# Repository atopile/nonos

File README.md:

# NONOS

### The Open Source Smart Speaker

<div align="center">

  **Premium Sound • Privacy First • Fully Hackable**

</div>

---

## 🎵 Experience Audio Freedom

NONOS is a premium smart speaker that puts you in control. It delivers exceptional sound quality while respecting your privacy, and its hardware is described declaratively in lightweight `.ato` files.

### ✨ Key Features

<table>
<tr>
<td width="50%">

**🔊 Audiophile-Grade Sound**

- Dual-driver system with dedicated tweeter and full-range speaker
- Texas Instruments TAS5825M Class-D amplifier
- Analog Devices ADAU145x DSP for pristine audio processing
- I2S digital audio interface for lossless playback

</td>
<td width="50%">

**🧠 Powerful Computing**

- Raspberry Pi CM5 module at its heart
- Gigabit Ethernet connectivity
- USB-C with Power Delivery support
- Multiple I2C, UART, and GPIO interfaces

</td>
</tr>
<tr>
<td width="50%">

**🎨 Interactive Design**

- 23 SK6805 addressable RGB LEDs
- Capacitive touch controls with volume slider
- NFC tap-to-pair functionality
- Minimalist cylindrical form factor

</td>
<td width="50%">

**⚡ Smart Power Management**

- USB-C Power Delivery (20V input)
- Efficient buck converters (5V & 3.3V rails)
- STUSB4500 PD controller
- Low standby power consumption

</td>
</tr>
</table>

---

## 🎶 Software Features

### Streaming Services

Connect and play from all your favorite sources:

- **Spotify Connect** - Stream directly from the Spotify app
- **AirPlay** - Native support for Apple devices
- **Bluetooth Audio** - Auto-pairing A2DP streaming
- **Local Playback** - Play your music library via network shares

### Smart Controls

Intuitive touch interface with gesture support:

- **Play/Pause** - Center button for media control
- **Track Navigation** - Skip tracks or seek within songs
- **Volume Slider** - 5-position touch slider with double-tap gestures
  - Double-tap position 0 for mute
  - Double-tap position 4 for +6dB boost
- **Configurable EQ** - 15-band parametric equalizer

### Audio Excellence

Professional-grade DSP processing:

- **Crossover Networks** - Optimized for dual-driver configuration
- **Dynamic Range Control** - Independent limiting for highs and lows
- **Mid-Side Processing** - Adjustable stereo width
- **PipeWire Integration** - Low-latency audio with automatic resampling

---

## 🎛️ Hardware Highlights

### Audio Processing Pipeline

```
CM5 (Digital Audio) → I2S → ADAU145x DSP → I2S → TAS5825M Amplifier → Speakers
```

### Interactive Hat Module

- **NFC**: PN5321 for instant device pairing
- **Touch**: CAP1188 capacitive sensor (3 buttons + 5-position slider)
- **LEDs**: 23x SK6805 RGB LEDs in a circular array
- **Level Shifting**: Ensures reliable 3.3V/5V communication

### Debug Headers

Three Saleae-compatible headers for easy development:

- UART console access
- I2C bus monitoring
- I2S audio stream analysis

### Printed Circuit Boards

#### Mainboard

- **atopile module:** `NONOS` (`elec/src/nonos.ato`)
- USB-C Power Delivery input via **STUSB4500** (up to 20 V)
- Power tree: **TPS54560x** 5 V buck ➜ **TLV75901** 3 .3 V LDO
- **Raspberry Pi CM5** compute module
- **ADAU145x** audio DSP ➜ **TAS5825M** 2-channel Class-D amplifier
- 10-pin mezzanine connector to the Hat
- Connectors for full-range & tweeter speakers
- Three Saleae-compatible debug headers (UART, I2C, I2S)

#### Control Hat

- **atopile module:** `Hat` (`elec/src/hat.ato`)
- **PN5321** NFC transceiver with custom button-antenna
- **CAP1188** capacitive touch sensor (3 buttons + 5-point slider)
- 23× **SK6805** side-emitting RGB LEDs arranged in a ring
- **74LVC1T45** level-shifter for reliable 5 V LED data
- Powered from 3 .3 V (logic) & 5 V (LEDs) supplied by the mainboard
- 10-pin mezzanine connector mates directly with the mainboard

---

## 🛠️ Hardware Design

The hardware is captured in concise `.ato` design files (powered by [atopile](https://atopile.io)).

```ato
module NONOS:
    """
    An opensource sonos era 100 clone
    """

    # Core Components
    cm5 = new CM5
    amplifier = new Texas_Instruments_TAS5825MRHBR_driver
    dsp = new Analog_Devices_ADAU145x_driver
    pd_controller = new STUSB4500

    # Smart Power Distribution
    pd_controller.power_out ~ power_20v
    power_20v ~> regulator_5v ~> power_5v
    power_5v ~> regulator_3v3 ~> power_3v3
```

### 📁 Project Structure

```
nonos/
├── elec/
│   └── src/
│       ├── nonos.ato      # Main speaker module
│       ├── hat.ato        # Touch/LED/NFC interface
│       └── parts/         # Component library
├── firmware/              # CM5 software stack
├── mechanical/            # Enclosure designs
└── docs/                  # Build instructions
```

---

## 🎚️ Audio Tuning

<table>
<tr>
<td width="33%"></td>
<td width="33%"></td>
<td width="33%"></td>
</tr>
</table>

Using a calibrated reference microphone we swept each driver, loaded the recordings into **Audacity** to eyeball the bumps and dips, then built FIR/biquad filters in SigmaStudio and dialed-in a 2-way crossover with gentle EQ to flatten the combined response. The whole process took about **20 heroic minutes**—roughly _twice_ the time it looks like Sonos spends on some of their launch-day tunings 😉.

---

## 🚀 Getting Started

### Prerequisites

- **[atopile](https://docs.atopile.io/atopile/quickstart)** compiler installed
- KiCad 8.0 or later (for PCB viewing/editing)
- Basic SMD soldering equipment

### Building NONOS

1. **Clone the repository**

   ```bash
   git clone https://github.com/atopile/nonos
   cd nonos
   ```

2. **Compile the hardware design**

   ```bash
   ato build
   ```

3. **Generate manufacturing files**

   ```bash
   ato build -t all
   ```

4. **Order PCBs and components**
   - Upload gerbers from `/build` to your preferred PCB manufacturer
   - Use the generated BOM for component ordering

---

## 🤝 Contributing

We love contributions! Whether it's:

- 🐛 Bug fixes
- ✨ New features
- 📚 Documentation improvements
- 🎨 Design enhancements

---

## 📄 License

NONOS is open source hardware, released under the MIT License. See [LICENSE](LICENSE) for details.

---

## 🌟 Acknowledgments

Built with ❤️ using **[atopile](https://atopile.io)** - the language that's revolutionizing hardware design.

Special thanks to the atopile community for making hardware development accessible to everyone.

---

<div align="center">
  
**Ready to build your own NONOS?**

[📖 Read the Docs](https://github.com/atopile/nonos) • [💬 Join Discord](https://discord.gg/7XSb5zTyfr) • [⭐ Star on GitHub](https://github.com/atopile/nonos)

</div>

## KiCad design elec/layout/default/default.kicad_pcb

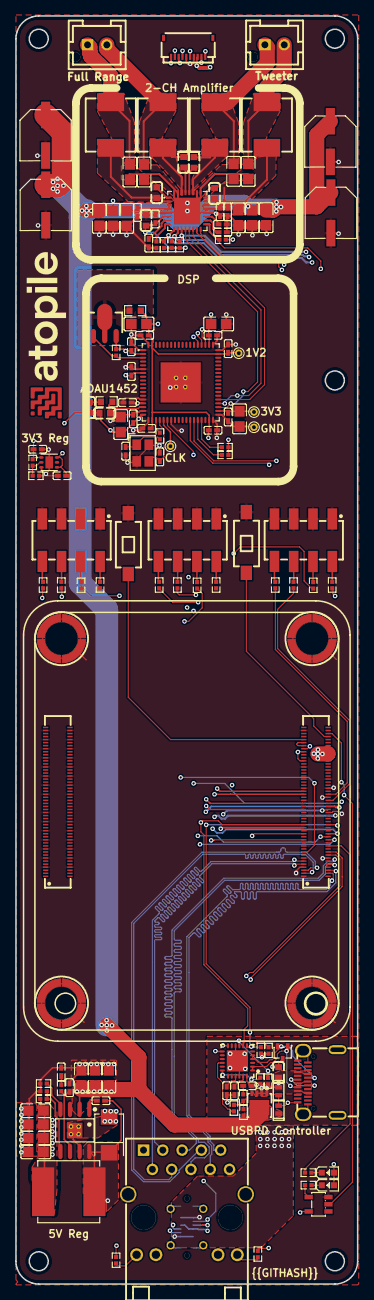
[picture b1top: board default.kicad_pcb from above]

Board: 4 copper layers, 45.0 x 167.0 mm, 141 parts (1 on the bottom side), 106 nets.

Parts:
C1, C4, C19, C21, C22, C31, C32: 1µF ±10% 25V X5R; C0402
C2: 4.7µF ±10% 16V X5R; C0603
C3, C33, C38, C39, C40, C41, C42, C43, C44, C45, C46, C47, C53, C54, C55: 100nF ±10% 16V X7R; C0402
C5, C6, C9, C10: 470nF ±10% 50V X7R; C0603
C7, C8, C11, C12: 680nF ±10% 50V X7R; C0805
C13, C14, C15, C16, C17, C18, C34, C35, C36, C37: 10µF ±10% 25V X5R; C0805
C20: 100nF ±10% 50V X7R; C0402
C23: 4.7nF ±5% 50V X7R; C0402
C24: 20pF ±5% 50V C0G; C0402
C25, C26, C27: 10µF ±10% 50V X5R; C0805
C28, C29, C52, C60: 22µF ±20% 25V X5R; C0805
C30: 4.7µF ±10% 35V X5R; C0603
C48, C49: 15pF ±5% 50V C0G; C0402
C50: 5.6nF ±10% 50V X7R; C0603
C51: 150pF ±5% 50V C0G; C0603
C56, C57, C58, C59: CAP-SMD_BD6.3-L6.6-W6.6-FD
CN1, CN2: CONN-SMD_DF40C-100DS-0.4V-51
D1: LED0603-RD-YELLOW
D2: LED0603-RD
D3: SMB_L4.6-W3.6-LS5.3-RD
D4: SOT-323-3_L2.1-W1.3-P1.32-LS2.1-BR
D5, D6: DFN1610-2_L1.6-W1.0-P1.05-RD
FPC1: FPC-SMD_10P-P0.50_HDGC_0.5K-HX-10PWB
HDR1, HDR2, HDR3: HDR-SMD_8P-P2.54-V-M-R2-C4-LS7.4
L1, L2, L3, L4: 10µH ±20% 4.5A 68mΩ; IND-SMD_L7.3-W6.8
L5: IND-SMD_L8.0-W8.0_SWPA8040S
Q1: PDFN3333-8_L3.1-W3.2-P0.65-LS3.4-BL
Q2: SOT-89-3_L4.5-W2.5-P1.50-LS4.1-TR
R1, R15, R16: 4.7kΩ ±1% 62.5mW; R0402
R2, R3, R4, R5, R35, R37, R40, R41: 10kΩ ±1% 62.5mW; R0402
R6, R7: 2kΩ ±1% 62.5mW; R0402
R8, R9: 470Ω ±1% 62.5mW; R0402
R10: 23.7kΩ ±1% 62.5mW; R0402
R11, R12, R14, R17, R24, R25, R26, R27, R28, R29, R30, R31, R32, R33, R34: 1kΩ ±1% 62.5mW; R0402
R13: 162kΩ ±1% 62.5mW; R0402
R18: 100kΩ ±1% 62.5mW; R0402
R19: 22kΩ ±1% 62.5mW; R0402
R20, R21: 100Ω ±1% 62.5mW; R0402
R22: 0Ω 100mW; R0603
R23: 4.3kΩ ±1% 100mW; R0603
R36: 47kΩ ±1% 62.5mW; R0402
R38: 54.9kΩ ±1% 62.5mW; R0402
RJ1: RJ45-TH_HR911130A
SW1, SW2: SW-SMD_L6.0-W3.3-LS8.0
TP1, TP2, TP3, TP4: TestPoint_THTPad_D1.0mm_Drill0.5mm
U1: VQFN-32_L5.0-W5.0-P0.50-TL-EP
U2: SOT-23-5_L3.0-W1.7-P0.95-LS2.8-BR
U3, U4, U5, U6: SMD_BD5.6-D4.1
U7: SOIC-8_L5.0-W4.0-P1.27-LS6.0-BL-EP2.0
U20: QFN-24_L4.0-W4.0-P0.50-BL-EP2.8
U21, U22: CONN-TH_B02B-XASK-1-A-LF-SN
U23: USB-C-SMD_HC-TYPE-C-24P-VS9.3-5A-F1.1-04
U24: LFCSP-72_L10.0-W10.0-P0.50-LS10.2-BL-EP5.3
U25: WSON-6_L2.0-W2.0-P0.65-TL-EP
USB1: USB-C-SMD_TYC-324G
X1: CRYSTAL-SMD_4P-L3.2-W2.5-BL-2

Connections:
3v3_vcc: C2.1, C3.1, C22.1, C34.1, C35.1, C37.1, C38.1, C43.1, C44.1, C45.1, C46.1, C47.1, C50.2, C51.2, CN1.39, CN1.42, CN1.43, D1.2, D2.2, FPC1.6, Q2.1, R2.2, R3.2, R4.2, R5.2, R8.1, R9.1, R11.1, R15.2, R16.2, R24.1, R36.1, R40.2, R41.2, TP3.1, U1.6, U2.5, U24.2, U24.7, U24.15, U24.18, U24.38, U24.56, U25.1
5v_vcc: C21.1, C28.1, C29.1, C52.1, C60.1, CN1.57, CN1.58, CN1.59, CN1.60, CN1.61, CN1.62, FPC1.8, L5.2, R12.1, R38.1, U25.4, U25.6
20v_vcc: C13.1, C14.1, C15.1, C16.1, C17.1, C18.1, C25.1, C26.1, C27.1, C53.1, C54.1, C55.1, C56.1, C57.1, C58.1, C59.1, D6.1, Q1.5, Q1.6, Q1.7, Q1.8, Q1.9, R18.2, U1.3, U1.4, U1.21, U1.22, U7.2
A5: D4.1, U20.1, U20.2, U23.A5, USB1.A5
ADR: R1.1, U1.8
AVDD: C1.1, U1.19
B5: D4.2, U20.4, U20.5, U23.B5, USB1.B5
BOOT: C20.1, U7.1
BST_Aneg_N: C5.1, U1.29
BST_Apos_P: C6.1, U1.1
BST_Bneg_N: C9.1, U1.28
BST_Bpos_P: C10.1, U1.24
CLKOUT: TP1.1, U24.23
COMP: C24.1, R10.1, U7.6
DISCH: R14.2, U20.9
ETH_LED_LINK: CN1.93, RJ1.12
ETH_LED_SPEED: CN1.92, RJ1.13
ETH_P0_N: CN1.5, RJ1.P3
ETH_P0_P: CN1.6, RJ1.P2
ETH_P1_N: CN1.3, RJ1.P7
ETH_P1_P: CN1.2, RJ1.P4
ETH_P2_N: CN1.96, RJ1.P6
ETH_P2_P: CN1.95, RJ1.P5
ETH_P3_N: CN1.98, RJ1.P9
ETH_P3_P: CN1.99, RJ1.P8
GVDD: C4.1, U1.18
OUT_Aneg_N: C5.2, L1.1, U1.30
OUT_Apos_P: C6.2, L2.1, U1.2
OUT_Bneg_N: C9.2, L3.1, U1.27
OUT_Bpos_P: C10.2, L4.1, U1.23
PLLFILT: C51.1, R23.1, U24.16
RT_CLK: R13.1, U7.4
RX: CN1.73, R26.1
VBUS_EN_SNK: R19.2, U20.16
VBUS_VS_DISCH: R17.2, U20.18
VDRIVE: Q2.3, R24.2, U24.3
VREG_1V2-VCC: C31.2, U20.21
VREG_2V7-VCC: C32.2, U20.23
VR_DIG: C19.1, U1.7
XTALIN_MCLK: R21.1, U24.21
XTALOUT: C49.1, U24.22, X1.3
Y: R7.2, U2.4
activity_led-cathode: D1.1, R6.1
activity_led_resistor-pins[20]: CN1.90, R6.2
address_bit_0: R40.1, U24.33
address_bit_1: R41.1, U24.32
amp_fault: CN1.17, R2.1, U1.9
amp_i2s_sck: U1.13, U24.40
amp_i2s_sd: U1.14, U24.41
amp_i2s_ws: U1.12, U24.39
amp_mute: CN1.78, R3.1, U1.10
amp_pdn: CN1.15, R4.1, U1.17
amp_warn: CN1.80, R5.1, U1.11
boot_mode: CN1.54, SW1.1
bootstrap_capacitor-cathode: C20.2, D3.1, L5.1, U7.8
c1-net: C50.1, R23.2
cm5-anode-0: R8.2, RJ1.11
cm5-anode-1: R9.2, RJ1.14
cm5-cathode: D2.1, R7.1
collector: Q2.2, R22.1
compensation_capacitors[0]-net: C23.1, R10.2
debug_headers[0]-_2: HDR1.2, R11.2
debug_headers[0]-_4: HDR1.4, R12.2
debug_headers[0]-_6: HDR1.6, R25.2
debug_headers[0]-_8: HDR1.8, R26.2
debug_headers[1]-_2: HDR2.2, R27.2
debug_headers[1]-_4: HDR2.4, R28.2
debug_headers[1]-_6: HDR2.6, R29.2
debug_headers[1]-_8: HDR2.8, R30.2
debug_headers[2]-_2: HDR3.2, R31.2
debug_headers[2]-_4: HDR3.4, R32.2
debug_headers[2]-_6: HDR3.6, R33.2
debug_headers[2]-_8: HDR3.8, R34.2
dsp_reset_disable: CN1.87, U24.24
eth_sync_out: CN1.9, R28.1
feedback_divider-output-VDIV_OUTPUT-0: R35.1, R36.2, U25.2
feedback_divider-output-VDIV_OUTPUT-1: R37.1, R38.2, U7.5
footprint-net-2: C33.1, R20.2
gate: Q1.4, R18.1, R19.1, R20.1
gnd: C1.2, C2.2, C3.2, C4.2, C7.2, C8.2, C11.2, C12.2, C13.2, C14.2, C15.2, C16.2, C17.2, C18.2, C19.2, C21.2, C22.2, C23.2, C24.2, C25.2, C26.2, C27.2, C28.2, C29.2, C30.1, C31.1, C32.1, C34.2, C35.2, C36.2, C37.2, C38.2, C39.2, C40.2, C41.2, C42.2, C43.2, C44.2, C45.2, C46.2, C47.2, C48.2, C49.2, C52.2, C53.2, C54.2, C55.2, C56.2, C57.2, C58.2, C59.2, C60.2, CN1.1, CN1.4, CN1.7, CN1.11, CN1.16, CN1.21, CN1.26, CN1.30, CN1.33, CN1.37, CN1.49, CN1.65, CN1.68, CN1.71, CN1.74, CN1.79, CN1.84, CN1.89, CN1.94, CN1.97, CN1.100, CN2.4, CN2.7, CN2.10, CN2.13, CN2.16, CN2.19, CN2.22, CN2.28, CN2.31, CN2.34, CN2.37, CN2.40, CN2.43, CN2.46, CN2.49, CN2.52, CN2.55, CN2.58, CN2.61, CN2.64, CN2.67, CN2.70, CN2.73, CN2.82, CN2.85, CN2.88, CN2.91, CN2.94, CN2.97, D3.2, D4.3, D5.2, D6.2, FPC1.5, FPC1.7, HDR1.1, HDR1.3, HDR1.5, HDR1.7, HDR2.1, HDR2.3, HDR2.5, HDR2.7, HDR3.1, HDR3.3, HDR3.5, HDR3.7, R1.2, R13.2, R35.2, R37.2, RJ1.SHIELD0, RJ1.SHIELD1, SW1.2, SW2.2, TP2.1, U1.5, U1.20, U1.25, U1.26, U1.31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
i2c-SCL: CN1.83, R15.1, R30.1, U1.16, U20.7, U24.31
i2c-SCLK: CN1.18, R16.1, R29.1, U1.15, U20.8, U24.30
i2cs[1]-SCL: CN1.28, FPC1.9
i2cs[1]-SDA: CN1.29, FPC1.10
i2s_ins[0]-SCK: CN1.76, R34.1, U24.57
i2s_ins[0]-SD: CN1.88, R32.1, U24.59
i2s_ins[0]-WS: CN1.13, R33.1, U24.58
input-pins[94]: CN1.53, U2.2
led_data: CN1.77, FPC1.1
nOE: C48.1, R21.2, X1.1
nfc_interrupt: CN1.25, FPC1.3
nfc_reset: CN1.86, FPC1.4
power_1v8-VCC: CN1.44, CN1.45
power_button: CN1.46, SW2.1
power_digital-VCC: C36.1, C39.1, C40.1, C41.1, C42.1, R22.2, TP4.1, U24.20, U24.35, U24.53, U24.71
power_vbus-VCC: C30.2, C33.2, D5.1, Q1.1, Q1.2, Q1.3, R14.1, R17.1, U20.24, U23.A4, U23.A9, U23.B4, U23.B9, USB1.A4, USB1.A9, USB1.B4, USB1.B9
spkr_full_n: C7.1, L1.2, U21.2
spkr_full_p: C8.1, L2.2, U21.1
spkr_tweet_n: C11.1, L3.2, U22.1
spkr_tweet_p: C12.1, L4.2, U22.2
touch_interrupt: CN1.23, FPC1.2
uart-SCLK: CN1.75, R25.1
usb_connector-usb2-USB_D-0_N: USB1.A7, USB1.B7
usb_connector-usb2-USB_D-0_P: USB1.A6, USB1.B6
usb_connector-usb2-USB_D-1_N: U23.A7, U23.B7
usb_connector-usb2-USB_D-1_P: U23.A6, U23.B6

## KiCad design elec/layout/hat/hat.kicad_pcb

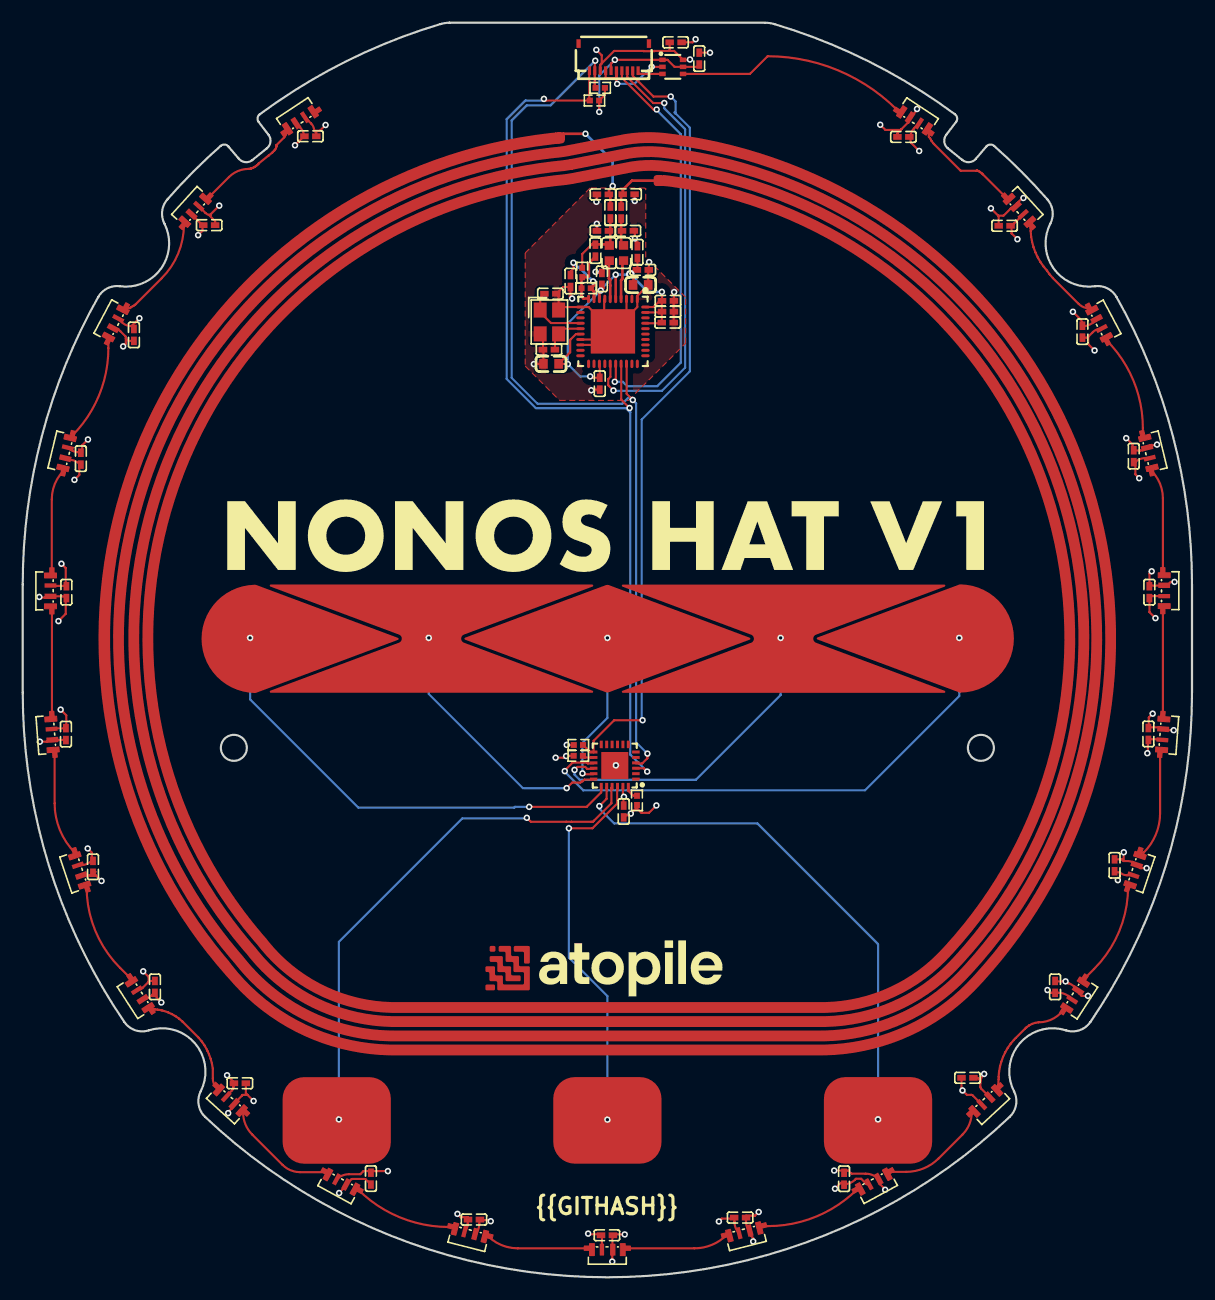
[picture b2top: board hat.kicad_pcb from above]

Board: 4 copper layers, 108.0 x 115.9 mm, 83 parts (0 on the bottom side), 52 nets.

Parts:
ANT1: hat-button-antenna
C1, C2, C3, C4, C5, C6, C7, C8, C9, C10, C11, C12, C14, C16, C17, C18, C19, C20, C21, C22, C23, C24, C25, C26, C27, C28, C29, C30, C34, C36, C37, C38, C39, C42, C43, C44, C45: 100nF ±10% 16V X7R; C0402
C13, C15: 100pF ±5% 50V C0G; C0402
C31, C32: 20pF ±5% 50V C0G; C0402
C33, C35: 10µF ±20% 6.3V X5R; C0603
C40, C41: 220pF ±10% 50V X7R; C0402
FPC1: FPC-SMD_10P-P0.50_HDGC_0.5K-HX-10PWB
L1, L2: IND-SMD_L1.6-W0.8-1
R1, R2, R6, R7: 10kΩ ±1% 62.5mW; R0402
R3: 100kΩ ±1% 62.5mW; R0402
R4, R5: 1kΩ ±1% 62.5mW; R0402
U1, U2, U3, U4, U5, U6, U8, U9, U10, U11, U12, U13, U14, U15, U16, U17, U18, U19, U20, U21, U22, U23, U24: LED-SMD_4P-L3.5-W1.6_SK6805SIDE-G-001
U7: QFN-40_L6.0-W6.0-P0.50-BL-EP4.1
U25: QFN-24_L4.0-W4.0-P0.50-BL-EP2.5
U26: SC-70-6_L2.2-W1.3-P0.65-LS2.1-BR
X1: CRYSTAL-SMD_4P-L3.2-W2.5-BL

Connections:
A: FPC1.10, U26.3
ADDR_COMM: R3.1, U25.14
B: U2.4, U26.4
GND: C1.2, C2.2, C3.2, C4.2, C5.2, C6.2, C7.2, C8.2, C9.2, C10.2, C11.2, C13.2, C15.2, C17.2, C18.2, C19.2, C20.2, C21.2, C22.2, C23.2, C24.2, C25.2, C26.2, C27.2, C28.2, C29.2, C30.2, C31.2, C32.2, C33.2, C34.2, C35.2, C36.2, C37.2, C38.2, C39.2, C40.2, C41.2, C42.2, C43.2, C44.2, C45.2, FPC1.4, FPC1.6, R3.2, R7.2, U1.2, U2.2, U3.2, U4.2, U5.2, U6.2, U7.1, U7.3, U7.7, U7.11, U7.17, U7.18, U7.41, U8.2, U9.2, U10.2, U11.2, U12.2, U13.2, U14.2, U15.2, U16.2, U17.2, U18.2, U19.2, U20.2, U21.2, U22.2, U23.2, U24.2, U25.25, U26.2, X1.2, X1.4
OSCIN: C31.1, U7.14, X1.1
OSCOUT: C32.1, U7.15, X1.3
P70_IRQ: FPC1.8, U7.25
RESET: R7.1, U25.24
RSTOUT_N: FPC1.7, U7.26
RX: C12.2, R4.2, R5.2, U7.10
SCL: FPC1.2, R2.1, U7.28, U25.4
SDA: FPC1.1, R1.1, U7.27, U25.3
TX1: L1.2, U7.4
TX2: L2.2, U7.6
antenna_N: ANT1.9, C15.1, C16.2
antenna_P: ANT1.10, C13.1, C14.2
data_out-DIN: U3.4, U24.1
leds[1]-data_in-DIN: U2.1, U13.4
leds[2]-data_in-DIN: U13.1, U17.4
leds[3]-data_in-DIN: U17.1, U18.4
leds[4]-data_in-DIN: U18.1, U19.4
leds[5]-data_in-DIN: U19.1, U20.4
leds[6]-data_in-DIN: U20.1, U21.4
leds[7]-data_in-DIN: U21.1, U22.4
leds[8]-data_in-DIN: U22.1, U23.4
leds[9]-data_in-DIN: U23.1, U24.4
leds[11]-data_in-DIN: U3.1, U4.4
leds[12]-data_in-DIN: U4.1, U5.4
leds[13]-data_in-DIN: U5.1, U6.4
leds[14]-data_in-DIN: U1.4, U6.1
leds[15]-data_in-DIN: U1.1, U8.4
leds[16]-data_in-DIN: U8.1, U9.4
leds[17]-data_in-DIN: U9.1, U10.4
leds[18]-data_in-DIN: U10.1, U11.4
leds[19]-data_in-DIN: U11.1, U12.4
leds[20]-data_in-DIN: U12.1, U14.4
leds[21]-data_in-DIN: U14.1, U15.4
leds[22]-data_in-DIN: U15.1, U16.4
nALERT_nBC_IRQ: FPC1.9, R6.1, U25.13
next_button: ANT1.3, U25.20
play_button: ANT1.2, U25.22
power-VCC: C29.1, C30.1, C33.1, C34.1, C35.1, C36.1, C37.1, C38.1, C39.1, C43.1, C44.1, FPC1.5, R1.2, R2.2, R6.2, U7.5, U7.8, U7.16, U7.23, U7.37, U7.39, U7.40, U25.23, U26.1, U26.5
power_b-VCC: C1.1, C2.1, C3.1, C4.1, C5.1, C6.1, C7.1, C8.1, C9.1, C10.1, C11.1, C17.1, C18.1, C19.1, C20.1, C21.1, C22.1, C23.1, C24.1, C25.1, C26.1, C27.1, C28.1, C45.1, FPC1.3, U1.3, U2.3, U3.3, U4.3, U5.3, U6.3, U8.3, U9.3, U10.3, U11.3, U12.3, U13.3, U14.3, U15.3, U16.3, U17.3, U18.3, U19.3, U20.3, U21.3, U22.3, U23.3, U24.3, U26.6
power_vmid-VCC: C42.1, R5.1, U7.9
prev_button: ANT1.1, U25.21
slider[0]: ANT1.4, U25.19
slider[1]: ANT1.5, U25.18
slider[2]: ANT1.6, U25.17
slider[3]: ANT1.7, U25.16
slider[4]: ANT1.8, U25.15
tx_1_mid: C14.1, C40.1, L1.1
tx_2_mid: C12.1, C16.1, C41.1, L2.1, R4.1

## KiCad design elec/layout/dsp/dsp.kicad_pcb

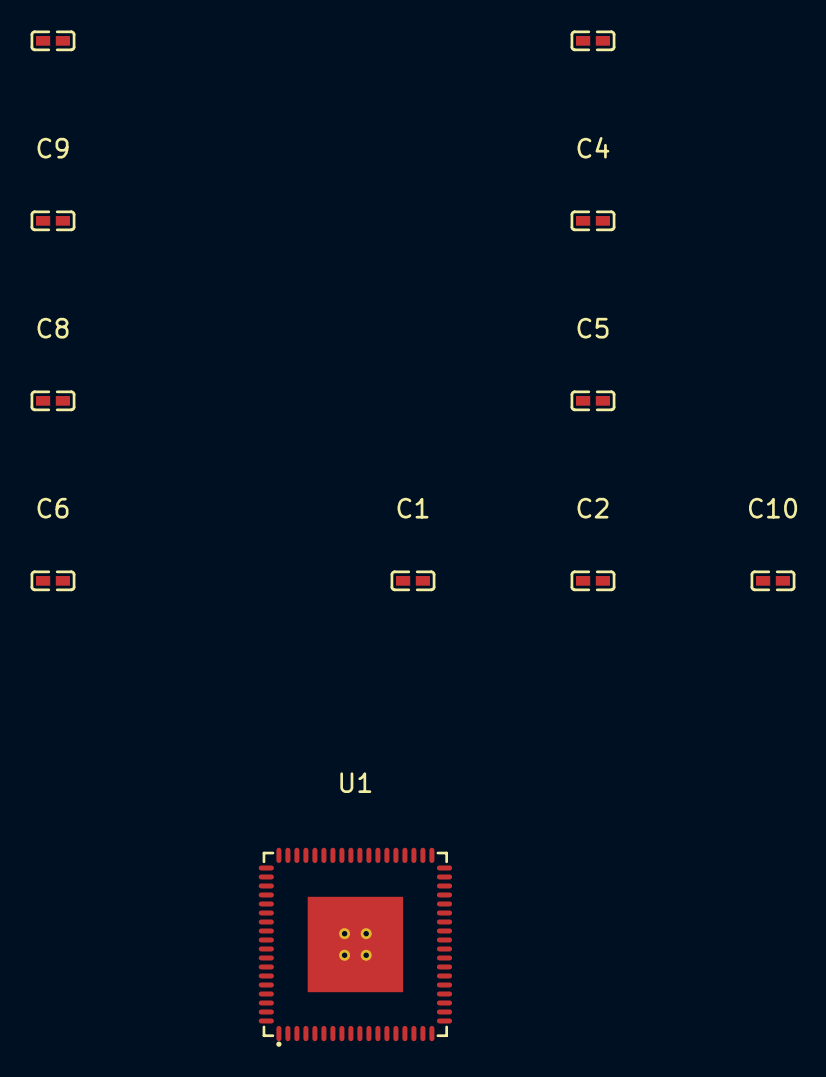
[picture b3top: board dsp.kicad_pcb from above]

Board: 2 copper layers, 11 parts (0 on the bottom side), 5 nets, no tracks yet.

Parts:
C1, C2, C3, C4, C5, C6, C7, C8, C9, C10: 100nF ±10% 16V X7R; C0402
U1: LFCSP-72_L10.0-W10.0-P0.50-LS10.2-BL-EP5.3

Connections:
MISO_SDA: U1.29, U1.30
N_DVDD: C2.1, C3.1, C4.1, C5.1, U1.20, U1.35, U1.53, U1.71
SCLK_SCL: U1.28, U1.31
gnd: C1.2, C2.2, C3.2, C4.2, C5.2, C6.2, C7.2, C8.2, C9.2, C10.2, U1.1, U1.6, U1.14, U1.17, U1.19, U1.25, U1.36, U1.37, U1.54, U1.55, U1.72, U1.73
hv: C1.1, C6.1, C7.1, C8.1, C9.1, C10.1, U1.2, U1.7, U1.15, U1.18, U1.38, U1.56

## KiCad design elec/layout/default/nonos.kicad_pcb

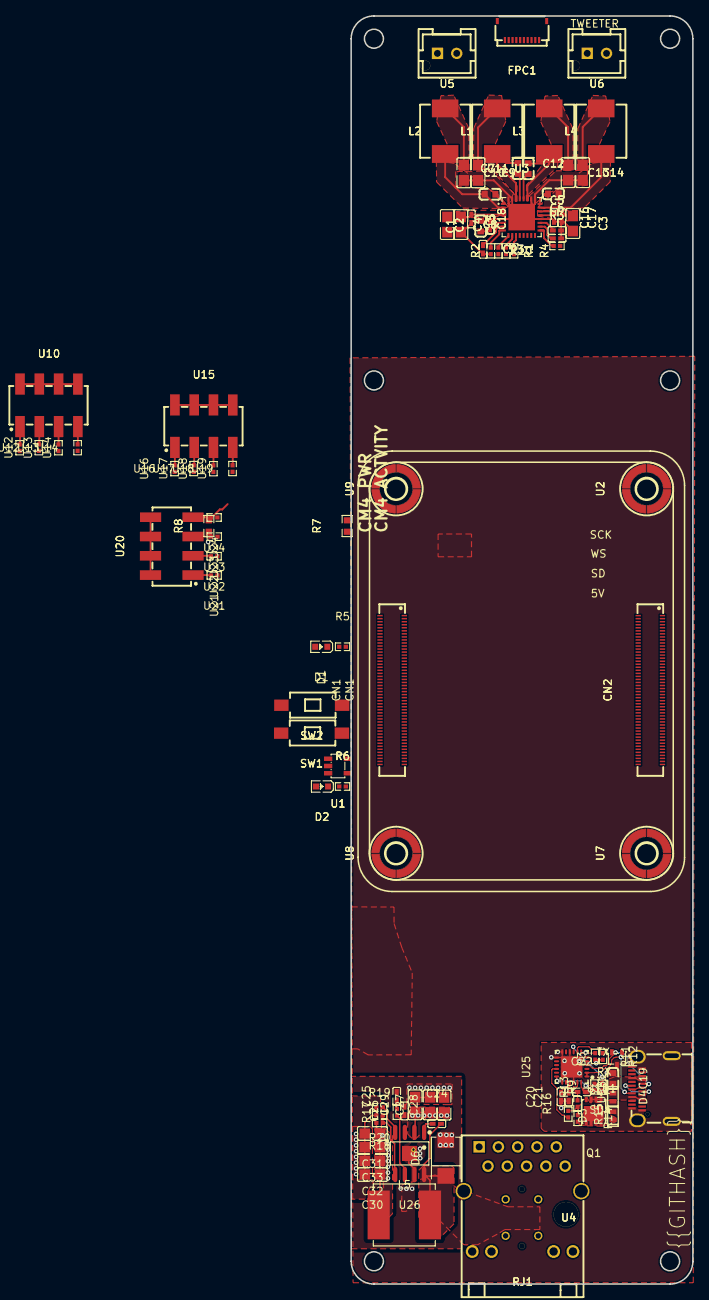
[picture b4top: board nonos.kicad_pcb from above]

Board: 4 copper layers, 45.0 x 167.0 mm, 98 parts (1 on the bottom side), 71 nets.

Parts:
C1: 4.7µF ±10% 10V X5R; C0603-bd72f6
C2, C16, C17, C18, C22: 100nF ±10% 16V X7R; C0402-b3ef17
C3, C4, C15, C30, C31, C32, C33: 22µF ±20% 25V X5R; C0805-3b2e55
C5, C6, C20, C21, C23: 1µF ±10% 25V X5R; C0402-b3ef17
C7, C8, C11, C12: 470nF ±10% 50V X7R; C0603-bd72f6
C9, C10, C13, C14: 680nF ±10% 50V X7R; C0805-3b2e55
C19: 4.7µF ±10% 35V X5R; C0603-bd72f6
C24: 100nF ±10% 50V X7R; C0402-b3ef17
C25: 4.7nF ±5% 50V C0G; C0402-b3ef17
C26: 8.2pF ±5% 50V C0G; C0402-b3ef17
C27, C28, C29: 10µF ±10% 50V X5R; C0805-3b2e55
CN1, CN2: CONN-SMD_DF40C-100DS-0.4V-51-ceffa9
D1: LED0603-RD-YELLOW-5af84a
D2: LED0603-RD-c81ffb
D3: SOT-323-3_L2.1-W1.3-P1.32-LS2.1-BR-ee9edb
D4, D5: DFN1610-2_L1.6-W1.0-P1.05-RD-57a24e
D6: SMB_L4.6-W3.6-LS5.3-RD-330cb3
FPC1: FPC-SMD_10P-P0.50_HDGC_0.5K-HX-10PWB-40cf1c
L1, L2, L3, L4: IND-SMD_L7.3-W6.8-0bbdba
L5: IND-SMD_L8.0-W8.0_SWPA8040S-2a70f8
Q1: PDFN3333-8_L3.1-W3.2-P0.65-LS3.4-BL-33e04e
R1, R2, R3, R4, R18: 10kΩ ±1% 62.5mW; R0402-56259e
R5, R6: 2kΩ ±1% 62.5mW; R0402-56259e
R7, R8: 470Ω ±1% 100mW; R0603-ebcab9
R9, R13, R19: 1kΩ ±1% 62.5mW; R0402-56259e
R10: 0Ω 62.5mW; R0402-56259e
R11, R12: 4.7kΩ ±1% 62.5mW; R0402-56259e
R14: 100kΩ ±1% 62.5mW; R0402-56259e
R15: 22kΩ ±1% 62.5mW; R0402-56259e
R16: 100Ω ±1% 62.5mW; R0402-56259e
R17: 23.7kΩ ±1% 62.5mW; R0402-56259e
R20: 162kΩ ±1% 62.5mW; R0402-56259e
RJ1: RJ45-TH_HR911130A-5845d4
SW1, SW2: SW-SMD_L6.0-W3.3-LS8.0-cfbaed
U1: SOT-23-5_L3.0-W1.7-P0.95-LS2.8-BR-9d80aa
U2, U7, U8, U9: SMD_BD5.6-D4.1-12eb58
U3: VQFN-32_L5.0-W5.0-P0.50-TL-EP-7b5304
U4: USB-C-SMD_HC-TYPE-C-24P-VS9.3-5A-F1.1-04-81dd06
U5, U6: CONN-TH_B02B-XASK-1-A-LF-SN-8344ff
U10, U15, U20: HDR-SMD_8P-P2.54-V-M-R2-C4-LS7.4
U11, U12, U13, U14, U16, U17, U18, U19, U21, U22, U23, U24: 1kΩ ±1% 62.5mW; R0402-56259e
U25: QFN-24_L4.0-W4.0-P0.50-BL-EP2.8-2a85a7
U26: SOIC-8_L5.0-W4.0-P1.27-LS6.0-BL-EP2.0-748c0f
USB1: USB-C-SMD_TYC-324G-a50b79

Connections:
ADR: R10.1, U3.8
AVDD: C5.1, U3.19
BOOT: C24.1, U26.1
BST_A_: C7.1, U3.29
BST_Aplus: C8.1, U3.1
BST_B_: C11.1, U3.28
BST_Bplus: C12.1, U3.24
CC1: D3.1, U4.A5, U25.1, U25.2, USB1.A5
CC2: D3.2, U4.B5, U25.4, U25.5, USB1.B5
COMP: C26.1, R17.1, U26.6
DISCH: R9.2, U25.9
DN2: U4.A7, U4.B7, USB1.A7, USB1.B7
DP1: U4.A6, U4.B6, USB1.A6, USB1.B6
FB: R18.1, R19.2, U26.5
GVDD: C6.1, U3.18
LRCLK: CN1.13, U3.12
MDI0plus: CN1.6, RJ1.P2
MDI1_: CN1.3, RJ1.P7
MDI1plus: CN1.2, RJ1.P4
MDI2plus: CN1.95, RJ1.P5
MDI3plus: CN1.99, RJ1.P8
OUT_A_: C7.2, L1.1, U3.30
OUT_Aplus: C8.2, L2.1, U3.2
OUT_B_: C11.2, L3.1, U3.27
OUT_Bplus: C12.2, L4.1, U3.23
PDNh: CN1.15, R3.1, U3.17
RT_CLK: R20.1, U26.4
SCLK: CN1.76, U3.13
SDIN: CN1.88, U3.14
SW: C24.2, D6.1, L5.1, U26.8
VBUS: C19.2, C22.2, D4.1, Q1.1, Q1.2, Q1.3, R9.1, R13.1, U4.A4, U4.A9, U4.B4, U4.B9, U25.24, USB1.A4, USB1.A9, USB1.B4, USB1.B9
VBUS_EN_SNK: R15.2, U25.16
VBUS_VS_DISCH: R13.2, U25.18
VR_DIG: C23.1, U3.7
Y: R6.2, U1.4
cm5-pins[4]-1: CN1.98, RJ1.P9
cm5-pins[8]: CN1.96, RJ1.P6
cm5-pins[9]: CN1.5, RJ1.P3
cm5-pins[14]: CN1.93, RJ1.12
cm5-pins[16]: CN1.92, RJ1.13
cm5-pins[92]: CN1.54, SW1.1
cm5.cm5-cathode: D1.1, R5.1
cm5.cm5-cathode-1: D2.1, R6.1
cm5.cm5-pins[20]: CN1.90, R5.2
cm5.cm5-pins[89]-1: CN1.44, CN1.45
cm5.cm5-pins[94]: CN1.53, U1.2
cm5.rj45-anode: R8.2, RJ1.14
cm5.rj45-anode-1: R7.2, RJ1.11
gate: Q1.4, R14.1, R15.1, R16.1
gnd: C1.2, C2.2, C3.2, C4.2, C5.2, C6.2, C9.2, C10.2, C13.2, C14.2, C15.2, C16.2, C17.2, C18.2, C19.1, C20.1, C21.1, C23.2, C25.2, C26.2, C27.2, C28.2, C29.2, C30.2, C31.2, C32.2, C33.2, CN1.1, CN1.4, CN1.7, CN1.11, CN1.16, CN1.21, CN1.26, CN1.30, CN1.33, CN1.37, CN1.49, CN1.65, CN1.68, CN1.71, CN1.74, CN1.79, CN1.84, CN1.89, CN1.94, CN1.97, CN1.100, CN2.4, CN2.7, CN2.10, CN2.13, CN2.16, CN2.19, CN2.22, CN2.28, CN2.31, CN2.34, CN2.37, CN2.40, CN2.43, CN2.46, CN2.49, CN2.52, CN2.55, CN2.58, CN2.61, CN2.64, CN2.67, CN2.70, CN2.73, CN2.82, CN2.85, CN2.88, CN2.91, CN2.94, CN2.97, D3.3, D4.2, D5.2, D6.2, FPC1.5, FPC1.8, R10.2, R18.2, R20.2, RJ1.SHIELD0, RJ1.SHIELD1, SW1.2, SW2.2, U1.3, U2.1, U2.2, U2.3, U2.4, U3.5, U3.20, U3.25, U3.26, U3.31, U3.32, U3.33, U4.25, U4.26, U4.27, U4.28, U4.A1, U4.A12, U4.B1, U4.B12, U7.1, U7.2, U7.3, U7.4, U8.1, U8.2, U8.3, U8.4, U9.1, U9.2, U9.3, U9.4, U25.6, U25.10, U25.12, U25.13, U25.22, U25.25, U26.7, U26.9, USB1.1, USB1.2, USB1.3, USB1.4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
hv: C1.1, C2.1, CN1.39, CN1.42, CN1.43, D1.2, D2.2, FPC1.6, R1.2, R2.2, R3.2, R4.2, R7.1, R8.1, R11.2, R12.2, U1.5, U3.6
hv-1: C30.1, C31.1, C32.1, C33.1, CN1.57, CN1.58, CN1.59, CN1.60, CN1.61, CN1.62, FPC1.7, L5.2, R19.1
hv-2: C3.1, C4.1, C15.1, C16.1, C17.1, C18.1, C27.1, C28.1, C29.1, D5.1, Q1.5, Q1.6, Q1.7, Q1.8, Q1.9, R14.2, U3.3, U3.4, U3.21, U3.22, U26.2
line: C14.1, L4.2, U6.1
line-2: CN1.28, R2.1, U3.10
line-3: C9.1, L1.2, U5.2
line-4: CN1.22, FPC1.1
line-5: CN1.83, FPC1.9, R11.1, U3.16, U25.7
line-6: C10.1, L2.2, U5.1
line-7: CN1.81, FPC1.3
line-8: CN1.82, FPC1.4
line-10: CN1.18, FPC1.10, R12.1, U3.15, U25.8
line-11: C13.1, L3.2, U6.2
line-12: CN1.20, FPC1.2
pd_controller.pd_controller-hv: C20.2, U25.21
pd_controller.pd_controller-hv-1: C21.2, U25.23
pd_controller.pd_controller-net: C22.1, R16.2
pins[33]: CN1.17, R1.1, U3.9
pins[53]: CN1.27, R4.1, U3.11
pins[91]: CN1.46, SW2.1
regulator_5v-net: C25.1, R17.2

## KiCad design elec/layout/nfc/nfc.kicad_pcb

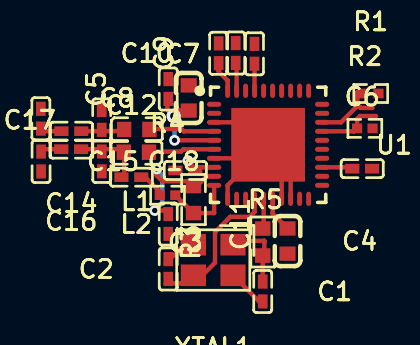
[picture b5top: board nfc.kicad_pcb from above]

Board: 2 copper layers, 27 parts (0 on the bottom side), 18 nets.

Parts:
C1, C2, C3, C5, C6, C7, C9, C10, C11, C12: 100nF ±10% 16V X7R; C0402-b3ef17
C4, C8: 10µF ±10% 10V X5R; C0603-bd72f6
C13, C15: 100pF ±5% 50V C0G; C0402-b3ef17
C14, C16: 22pF ±5% 50V C0G; C0402-b3ef17
C17, C18: 220pF ±10% 50V X7R; C0402-b3ef17
L1, L2: IND-SMD_L1.6-W0.8-1-cea827
R1, R2: 100kΩ ±1% 62.5mW; R0402-56259e
R3, R5: 10kΩ ±1% 100mW; R0603-ebcab9
R4: 1kΩ ±1% 62.5mW; R0402-56259e
U1: QFN-40_L6.0-W6.0-P0.50-BL-EP4.1-54a13c
XTAL1: CRYSTAL-SMD_4P-L3.2-W2.5-BL-e199c8

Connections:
MOSI_SDA_HSU_TX: R1.1, U1.28
NSS_P50_SCL_HSU_RX: R2.1, U1.27
OSCIN: C2.1, U1.14, XTAL1.3
OSCOUT: R3.2, U1.15
RX: R4.2, R5.2, U1.10
SVDD: C7.1, U1.37
TX1: L1.2, U1.4
TX2: L2.2, U1.6
VMID: C11.1, R5.1, U1.9
gnd: C1.2, C2.2, C3.2, C4.2, C5.2, C6.2, C7.2, C8.2, C9.2, C10.2, C11.2, C13.2, C15.2, C17.2, C18.2, U1.1, U1.3, U1.7, U1.11, U1.17, U1.18, U1.41, XTAL1.2, XTAL1.4
hv: C3.1, C4.1, C5.1, C6.1, C8.1, C9.1, C10.1, U1.5, U1.8, U1.16, U1.23, U1.39, U1.40
hv-1: R1.2, R2.2
line: C15.1, C16.2
line-1: C13.1, C14.2
net: C12.2, R4.1
oscillator-net: C1.1, R3.1, XTAL1.1
tx_1_mid: C14.1, C17.1, L1.1
tx_2_mid: C12.1, C16.1, C18.1, L2.1

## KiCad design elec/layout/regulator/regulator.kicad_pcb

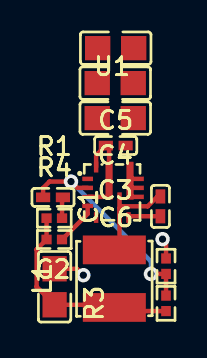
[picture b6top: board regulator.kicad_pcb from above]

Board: 2 copper layers, 13 parts (0 on the bottom side), 8 nets.

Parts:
C1, C6: 100nF ±10% 16V X7R; C0402
C2: 100pF ±5% 50V C0G; C0402
C3, C4, C5: 4.7µF ±10% 25V X5R; C0805
C7: 47µF ±20% 6.3V X5R; C0805
L1: 3.3µH ±20% 4A 73mΩ; IND-SMD_L4.0-W4.0
R1: 22kΩ ±1% 62.5mW; R0402
R2: 8.2kΩ ±1% 62.5mW; R0402
R3: 68kΩ ±1% 62.5mW; R0402
R4: 100kΩ ±1% 62.5mW; R0402
U1: _Texas_Instruments_TPS56637RPAR; VQFN-HR-10_L3.0-W3.0_RPA

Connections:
net: C3.1, C4.1, C5.1, C6.1, U1.8
net-1: C3.2, C4.2, C5.2, C6.2, C7.2, R2.1, U1.3, U1.9, U1.10
net-2: C7.1, L1.1, R1.1, R3.1, R4.1
net-3: R4.2, U1.4
net-4: C2.1, R1.2
net-5: C2.2, R2.2, R3.2, U1.2
net-6: C1.2, L1.2, U1.6
net-7: C1.1, U1.7

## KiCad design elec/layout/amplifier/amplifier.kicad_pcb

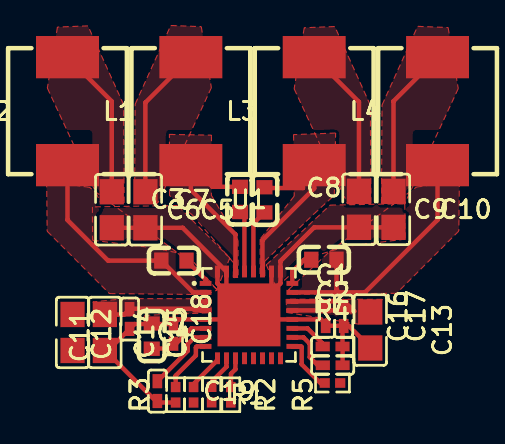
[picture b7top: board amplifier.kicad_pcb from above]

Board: 2 copper layers, 29 parts (0 on the bottom side), 23 nets.

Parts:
C1, C2, C19: 1µF ±10% 25V X5R; C0402-b3ef17
C3, C4, C7, C8: 470nF ±10% 50V X7R; C0603-bd72f6
C5, C6, C9, C10: 680nF ±10% 50V X7R; C0805-3b2e55
C11: 4.7µF ±10% 10V X5R; C0603-bd72f6
C12, C16, C17, C18: 100nF ±10% 16V X7R; C0402-b3ef17
C13, C14, C15: 22µF ±20% 25V X5R; C0805-3b2e55
L1, L2, L3, L4: IND-SMD_L7.3-W6.8-0bbdba
R1: 10Ω ±1% 62.5mW; R0402-56259e
R2, R3, R4, R5: 10kΩ ±1% 62.5mW; R0402-56259e
U1: VQFN-32_L5.0-W5.0-P0.50-TL-EP-7b5304

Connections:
ADR: R1.1, U1.8
AVDD: C1.1, U1.19
BST_A_: C3.1, U1.29
BST_Aplus: C4.1, U1.1
BST_B_: C7.1, U1.28
BST_Bplus: C8.1, U1.24
DVDD: C11.1, C12.1, U1.6
GPIO0: R2.1, U1.9
GPIO1: R3.1, U1.10
GPIO2: R5.1, U1.11
GVDD: C2.1, U1.18
OUT_A_: C3.2, L1.1, U1.30
OUT_Aplus: C4.2, L2.1, U1.2
OUT_B_: C7.2, L3.1, U1.27
OUT_Bplus: C8.2, L4.1, U1.23
PDNh: R4.1, U1.17
PVDD: C13.1, C14.1, C15.1, C16.1, C17.1, C18.1, U1.3, U1.4, U1.21, U1.22
VR_DIG: C19.1, U1.7
gnd: C1.2, C2.2, C5.2, C6.2, C9.2, C10.2, C11.2, C12.2, C13.2, C14.2, C15.2, C16.2, C17.2, C18.2, C19.2, R1.2, U1.5, U1.20, U1.25, U1.26, U1.31, U1.32, U1.33
line: C10.1, L4.2
line-1: C6.1, L2.2
line-2: C9.1, L3.2
line-3: C5.1, L1.2

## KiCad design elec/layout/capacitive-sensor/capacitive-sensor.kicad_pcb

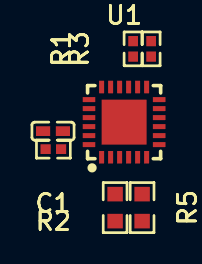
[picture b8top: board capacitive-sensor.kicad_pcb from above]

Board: 2 copper layers, 7 parts (0 on the bottom side), 7 nets, no tracks yet.

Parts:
C1: 100nF ±10% 16V X7R; C0402-b3ef17
R1, R2, R3: 10kΩ ±1% 62.5mW; R0402-56259e
R4, R5: 10kΩ ±1% 100mW; R0603-ebcab9
U1: QFN-24_L4.0-W4.0-P0.50-BL-EP2.5-58dc27

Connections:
ADDR_COMM: R1.1, U1.14
ALERTh_BC_IRQh: R3.1, U1.13
RESET: R2.1, U1.24
SMCLK_BC_CLK_SPI_CLK: R4.1, U1.4
SMDATA_BC_DATA_SPI_MSIO_SPI_MISO: R5.1, U1.3
gnd: C1.2, R1.2, R2.2, U1.25
hv: C1.1, R3.2, R4.2, R5.2, U1.23

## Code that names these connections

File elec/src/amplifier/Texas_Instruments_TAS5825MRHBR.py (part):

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    #     modules, interfaces, parameters
    # ----------------------------------------
    # TODO: Change auto-generated interface types to actual high level types
    BST_Aplus: F.Electrical  # pin: 1
    OUT_Aplus: F.Electrical  # pin: 2
    DGND: F.Electrical  # pin: 5
    DVDD: F.Electrical  # pin: 6
    VR_DIG: F.Electrical  # pin: 7
    ADR: F.Electrical  # pin: 8
    GPIO0: F.Electrical  # pin: 9
    GPIO1: F.Electrical  # pin: 10
    GPIO2: F.Electrical  # pin: 11
    LRCLK: F.Electrical  # pin: 12
    SCLK: F.Electrical  # pin: 13
    SDIN: F.Electrical  # pin: 14
    SDA: F.Electrical  # pin: 15
    SCL: F.Electrical  # pin: 16
    PDNh: F.Electrical  # pin: 17
    GVDD: F.Electrical  # pin: 18
    AVDD: F.Electrical  # pin: 19
    AGND: F.Electrical  # pin: 20
    PVDD: F.Electrical  # pins: 3, 4, 21, 22
    OUT_Bplus: F.Electrical  # pin: 23
    BST_Bplus: F.Electrical  # pin: 24
    PGND: F.Electrical  # pins: 25, 26, 31, 32
    OUT_B_: F.Electrical  # pin: 27
    BST_B_: F.Electrical  # pin: 28
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                "6": self.DVDD,
                "7": self.VR_DIG,
                "8": self.ADR,
                "9": self.GPIO0,
                "10": self.GPIO1,
                "11": self.GPIO2,
                "12": self.LRCLK,
                "13": self.SCLK,
                "14": self.SDIN,
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    """
    Dual Channel 38Wx1@8Ω VQFN-32(5x5) Audio Amplifiers ROHS

    I2C Slave Address Configuration (determined by ADR pin resistor to GND):

    | ADR PIN Resistance  | Address Bits | Address |
    |---------------------|--------------|---------|
    | 0 Ω                 | 1001100      | 0x4C    |
    | 1 kΩ                | 1001101      | 0x4D    |
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        self.i2s.sd.line.connect(self.amplifier.SDIN)

        # Control signals
        self.fault.line.connect(self.amplifier.GPIO0)
        self.mute.line.connect(self.amplifier.GPIO1)
        self.warn.line.connect(self.amplifier.GPIO2)
        self.pdn.line.connect(self.amplifier.PDNh)

        # Pullups for control signals
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
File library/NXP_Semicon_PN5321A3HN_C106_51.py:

# This file is part of the faebryk project
# SPDX-License-Identifier: MIT

import logging

import faebryk.library._F as F  # noqa: F401
from faebryk.core.module import Module
from faebryk.libs.library import L  # noqa: F401
from faebryk.libs.picker.picker import DescriptiveProperties
from faebryk.libs.units import P  # noqa: F401

logger = logging.getLogger(__name__)


class NXP_Semicon_PN5321A3HN_C106_51(Module):
    """
    TODO: Docstring describing your module

    QFN-40-EP(6x6) RFID ICs ROHS
    """

    # ----------------------------------------
    #     modules, interfaces, parameters
    # ----------------------------------------
    # TODO: Change auto-generated interface types to actual high level types
    DVSS: F.Electrical  # pin: 1
    LOADMOD: F.Electrical  # pin: 2
    TVSS1: F.Electrical  # pin: 3
    TX1: F.Electrical  # pin: 4
    TVDD: F.Electrical  # pin: 5
    TX2: F.Electrical  # pin: 6
    TVSS2: F.Electrical  # pin: 7
    AVDD: F.Electrical  # pin: 8
    VMID: F.Electrical  # pin: 9
    RX: F.Electrical  # pin: 10
    AVSS: F.Electrical  # pin: 11
    AUX1: F.Electrical  # pin: 12
    AUX2: F.Electrical  # pin: 13
    OSCIN: F.Electrical  # pin: 14
    OSCOUT: F.Electrical  # pin: 15
    I0: F.Electrical  # pin: 16
    I1: F.Electrical  # pin: 17
    TESTEN: F.Electrical  # pin: 18
    P35: F.Electrical  # pin: 19
    N_C_: F.Electrical  # pins: 20, 21, 22
    PVDD: F.Electrical  # pin: 23
    P30_UART_RX: F.Electrical  # pin: 24
    P70_IRQ: F.Electrical  # pin: 25
    RSTOUT_N: F.Electrical  # pin: 26
    NSS_P50_SCL_HSU_RX: F.Electrical  # pin: 27
    MOSI_SDA_HSU_TX: F.Electrical  # pin: 28
    MISO_P71: F.Electrical  # pin: 29
    SCK_P72: F.Electrical  # pin: 30
    P31_UART_TX: F.Electrical  # pin: 31
    P32_INT0: F.Electrical  # pin: 32
    P33_INT1: F.Electrical  # pin: 33
    P34_SIC_CLK: F.Electrical  # pin: 34
    SIGOUT: F.Electrical  # pin: 35
    SIGIN: F.Electrical  # pin: 36
    SVDD: F.Electrical  # pin: 37
    RSTPD_N: F.Electrical  # pin: 38
    DVDD: F.Electrical  # pin: 39
    VBAT: F.Electrical  # pin: 40
    EP: F.Electrical  # pin: 41

    # ----------------------------------------
    #                 traits
    # ----------------------------------------
    lcsc_id = L.f_field(F.has_descriptive_properties_defined)({"LCSC": "C880904"})
    designator_prefix = L.f_field(F.has_designator_prefix_defined)("U")
    descriptive_properties = L.f_field(F.has_descriptive_properties_defined)(
        {
            DescriptiveProperties.manufacturer: "NXP Semicon",
            DescriptiveProperties.partno: "PN5321A3HN/C106,51",
        }
    )
    datasheet = L.f_field(F.has_datasheet_defined)(
        "https://www.nxp.com/docs/en/nxp/data-sheets/PN532_C1.pdf"
    )

    @L.rt_field
    def attach_via_pinmap(self):
        return F.can_attach_to_footprint_via_pinmap(
            {
                "1": self.DVSS,
                "2": self.LOADMOD,
                "3": self.TVSS1,
                "4": self.TX1,
                "5": self.TVDD,
                "6": self.TX2,
                "7": self.TVSS2,
                "8": self.AVDD,
                "9": self.VMID,
                "10": self.RX,
                "11": self.AVSS,
                "12": self.AUX1,
                "13": self.AUX2,
                "14": self.OSCIN,
                "15": self.OSCOUT,
                "16": self.I0,
                "17": self.I1,
                "18": self.TESTEN,
                "19": self.P35,
                "20": self.N_C_,
                "21": self.N_C_,
                "22": self.N_C_,
                "23": self.PVDD,
                "24": self.P30_UART_RX,
                "25": self.P70_IRQ,
                "26": self.RSTOUT_N,
                "27": self.NSS_P50_SCL_HSU_RX,
                "28": self.MOSI_SDA_HSU_TX,
                "29": self.MISO_P71,
                "30": self.SCK_P72,
                "31": self.P31_UART_TX,
                "32": self.P32_INT0,
                "33": self.P33_INT1,
                "34": self.P34_SIC_CLK,
                "35": self.SIGOUT,
                "36": self.SIGIN,
                "37": self.SVDD,
                "38": self.RSTPD_N,
                "39": self.DVDD,
                "40": self.VBAT,
                "41": self.EP,
            }
        )

    def __preinit__(self):
        # ------------------------------------
        #           connections
        # ------------------------------------

        # ------------------------------------
        #          parametrization
        # ------------------------------------
        pass

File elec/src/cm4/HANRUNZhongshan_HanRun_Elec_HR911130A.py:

# This file is part of the faebryk project
# SPDX-License-Identifier: MIT

import logging

import faebryk.library._F as F  # noqa: F401
from faebryk.core.module import Module
from faebryk.libs.library import L  # noqa: F401
from faebryk.libs.units import P  # noqa: F401
from faebryk.libs.picker.picker import DescriptiveProperties


logger = logging.getLogger(__name__)


class _HANRUNZhongshan_HanRun_Elec_HR911130A(Module):
    """
    RJ45Receptacle 1 WithLED Plugin Ethernet Connectors / Modular Connectors (RJ45 RJ11) ROHS
    """

    # ----------------------------------------
    #     modules, interfaces, parameters
    # ----------------------------------------
    # TODO: Change auto-generated interface types to actual high level types
    MDI0plus: F.Electrical  # pin: MDI0+
    MDI0_: F.Electrical  # pin: MDI0-
    MDI1plus: F.Electrical  # pin: MDI1+
    MDI1_: F.Electrical  # pin: MDI1-
    MDI2plus: F.Electrical  # pin: MDI2+
    MDI2_: F.Electrical  # pin: MDI2-
    MDI3plus: F.Electrical  # pin: MDI3+
    MDI3_: F.Electrical  # pin: MDI3-
    P1: F.Electrical  # pin: P1
    P10: F.Electrical  # pin: P10
    SHIELD0: F.Electrical  # pin: SHIELD0
    SHIELD1: F.Electrical  # pin: SHIELD1
    unnamed = L.list_field(4, F.Electrical)

    link_led: F.LED
    speed_led: F.LED

    # ----------------------------------------
    #                 traits
    # ----------------------------------------
    lcsc_id = L.f_field(F.has_descriptive_properties_defined)({"LCSC": "C54408"})
    designator_prefix = L.f_field(F.has_designator_prefix_defined)("RJ")
    descriptive_properties = L.f_field(F.has_descriptive_properties_defined)(
        {
            DescriptiveProperties.manufacturer: "HANRUN(Zhongshan HanRun Elec)",
            DescriptiveProperties.partno: "HR911130A",
        }
    )
    datasheet = L.f_field(F.has_datasheet_defined)(
        "https://www.lcsc.com/datasheet/lcsc_datasheet_1811141815_HANRUN-Zhongshan-HanRun-Elec-HR911130A_C54408.pdf"
    )

    @L.rt_field
    def attach_via_pinmap(self):
        return F.can_attach_to_footprint_via_pinmap(
            {
                "11": self.unnamed[2],
                "12": self.unnamed[3],
                "13": self.unnamed[1],
                "14": self.unnamed[0],
                "P2": self.MDI0plus,
                "P3": self.MDI0_,
                "P4": self.MDI1plus,
                "P7": self.MDI1_,
                "P5": self.MDI2plus,
                "P6": self.MDI2_,
                "P8": self.MDI3plus,
                "P9": self.MDI3_,
                "P1": self.P1,
                "P10": self.P10,
                "SHIELD0": self.SHIELD0,
                "SHIELD1": self.SHIELD1,
            }
        )

    def __preinit__(self):
        # Connections
        self.link_led.cathode.connect(self.unnamed[2])
        self.link_led.anode.connect(self.unnamed[3])
        self.speed_led.cathode.connect(self.unnamed[0])
        self.speed_led.anode.connect(self.unnamed[1])
        
        # Parameters
        self.link_led.color.alias_is(F.LED.Color.GREEN)
        self.link_led.forward_voltage.alias_is(2.1 * P.V)
        self.link_led.max_current.alias_is(10 * P.mA)
        self.speed_led.color.alias_is(F.LED.Color.YELLOW)
        self.speed_led.forward_voltage.alias_is(2.1 * P.V)
        self.speed_led.max_current.alias_is(10 * P.mA)

class HANRUNZhongshan_HanRun_Elec_HR911130A(Module):
    """
    RJ45Receptacle 1 WithLED Plugin Ethernet Connectors / Modular Connectors (RJ45 RJ11) ROHS
    """

    ethernet: F.Ethernet
    power_led: F.ElectricPower
    connector: _HANRUNZhongshan_HanRun_Elec_HR911130A
    # link_led = L.f_field(F.LEDIndicator)(use_mosfet=False)
    # speed_led = L.f_field(F.LEDIndicator)(use_mosfet=False)

    link_led_resistor: F.Resistor
    speed_led_resistor: F.Resistor

    def __preinit__(self):
        self.ethernet.pairs[0].p.signal.connect(self.connector.MDI0plus)
        self.ethernet.pairs[0].n.signal.connect(self.connector.MDI0_)
        self.ethernet.pairs[1].p.signal.connect(self.connector.MDI1plus)
        self.ethernet.pairs[1].n.signal.connect(self.connector.MDI1_)
        self.ethernet.pairs[2].p.signal.connect(self.connector.MDI2plus)
        self.ethernet.pairs[2].n.signal.connect(self.connector.MDI2_)
        self.ethernet.pairs[3].p.signal.connect(self.connector.MDI3plus)
        self.ethernet.pairs[3].n.signal.connect(self.connector.MDI3_)

        # link and speed LEDs
        # self.ethernet.led_link.connect(self.link_led.logic_in)
        # self.ethernet.led_speed.connect(self.speed_led.logic_in)

        # self.link_led.led.led.specialize(self.connector.link_led)
        # self.speed_led.led.led.specialize(self.connector.speed_led)

        self.power_led.hv.connect_via([self.link_led_resistor, self.connector.link_led], self.ethernet.led_link.signal)
        self.power_led.hv.connect_via([self.speed_led_resistor, self.connector.speed_led], self.ethernet.led_speed.signal)

        self.link_led_resistor.resistance.constrain_subset(L.Range.from_center_rel(470 * P.ohm, 0.05))
        self.speed_led_resistor.resistance.constrain_subset(L.Range.from_center_rel(470 * P.ohm, 0.05))

        # shield
        self.ethernet.single_electric_reference.get_reference().lv.connect(
            self.connector.SHIELD0, self.connector.SHIELD1
        )

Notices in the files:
README.md:
License: MIT
